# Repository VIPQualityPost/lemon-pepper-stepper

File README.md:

# Lemon Pepper Stepper Driver
Small, all in one hybrid stepper + BLDC driver, designed to mount to the back of NEMA 14/17 size stepper motors. The board supports up to 48V @ 1.5A with a choice of either step-dir, CAN bus, I2C, UART or USB input. Additionally, there are 5 GPIO broken out that can be used for a second encoder (AB hardware encoder or I2C), endstops or other general purposes. Current sensing is also included on-board.
The boards can easily be assembled by JLC and the design has been cost-optimized, coming in at about $20 per board fully assembled (minus connectors, which need to be modified to sit flat on motor back). 

Due to the high pole pair count of stepper motors, a high resolution (21 bit) magnetic encoder is used, supporting both SPI and hardware ABI position encoding. 
Despite the rather high theoretical performance of this board I think you would need some serious cooling to actually hit the potential 50-70W specs of the parts. A heatsink has been designed and produced that works well with the board, giving a uniform back profile and small fins for heat dissipation.

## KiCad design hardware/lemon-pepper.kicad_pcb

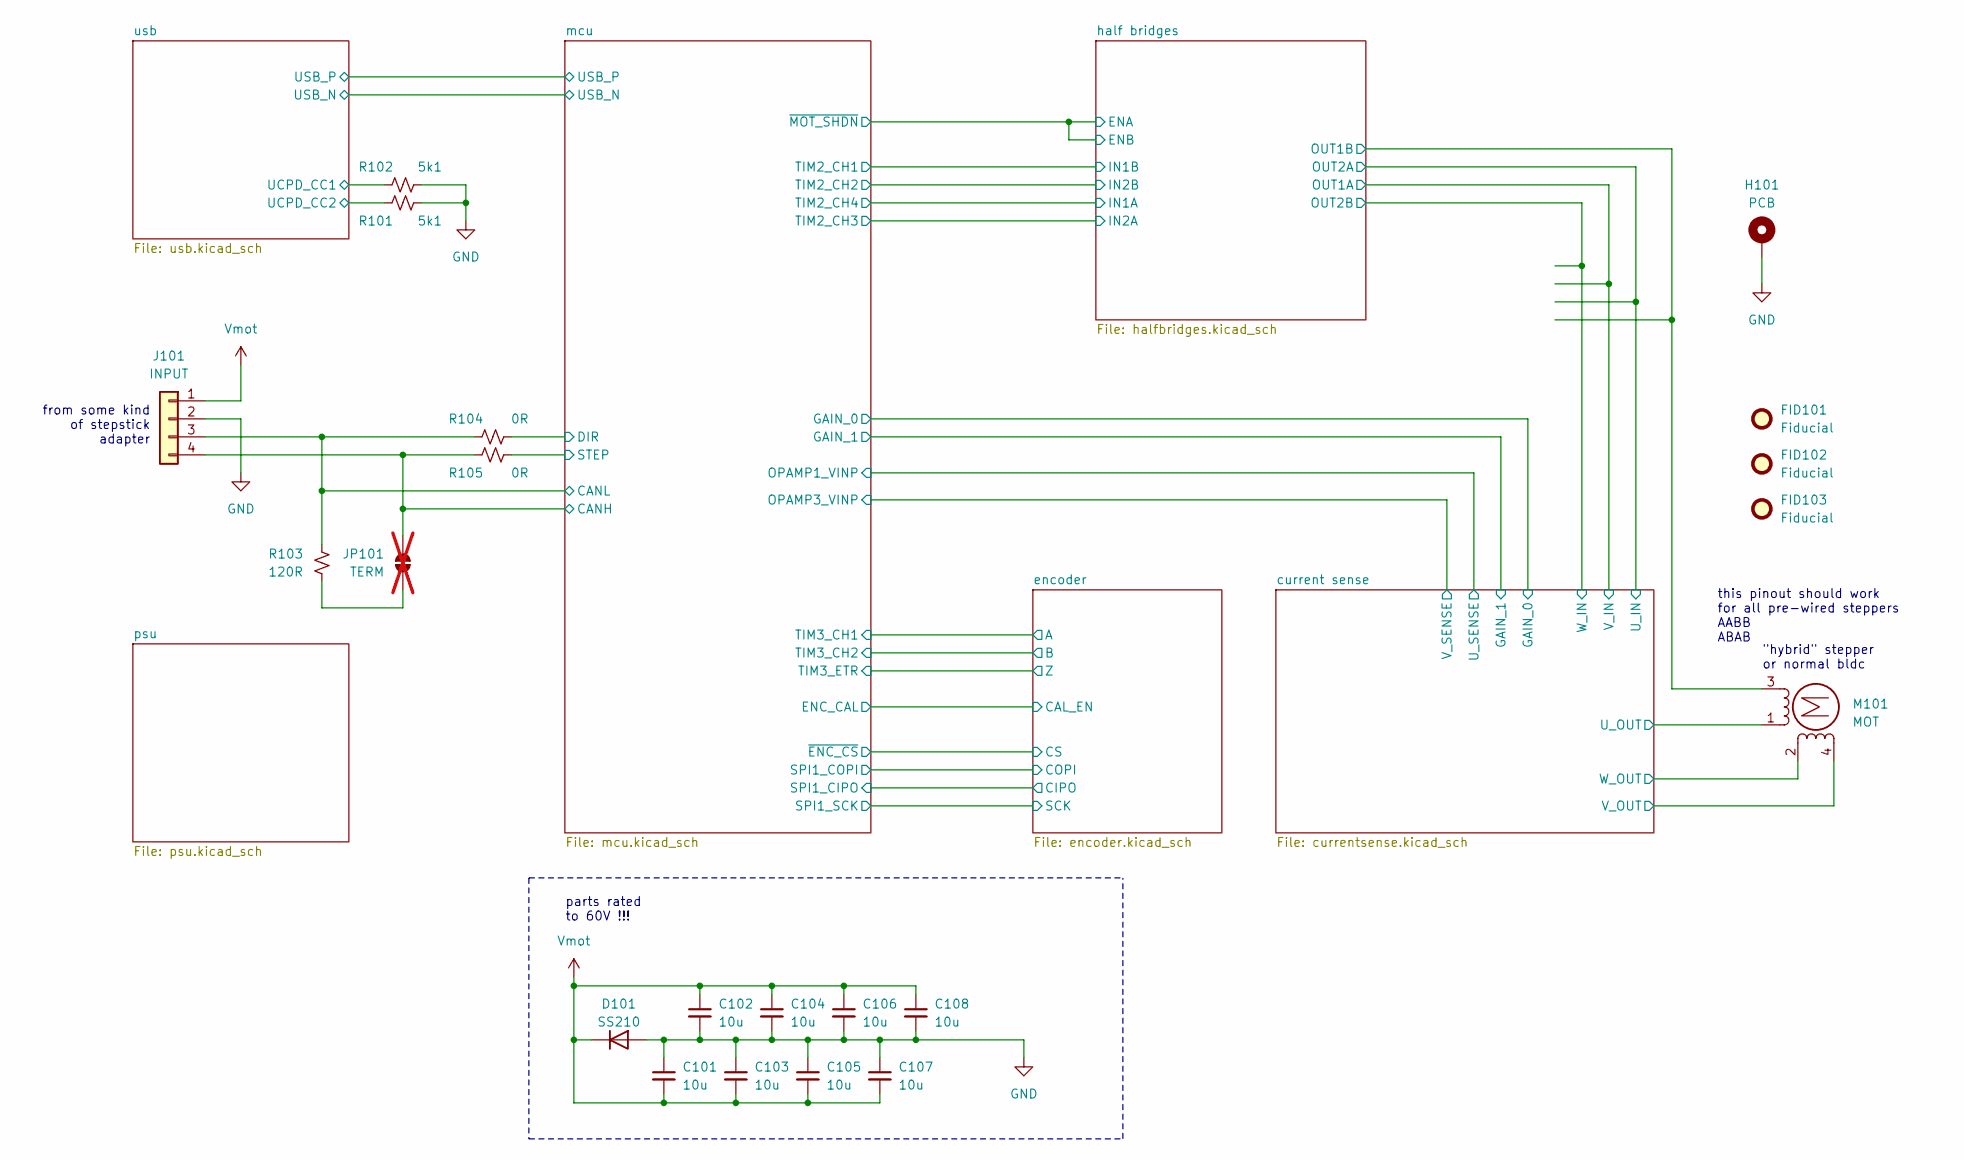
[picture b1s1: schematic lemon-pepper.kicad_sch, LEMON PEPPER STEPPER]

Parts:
C101, C102, C103, C104, C105, C106, C107, C108: 10u; C_0805_2012Metric; LCSC ID C440198
D101: SS210; D_SMA; LCSC ID C14996
FID101, FID102, FID103: Fiducial; Fiducial_0.5mm_Mask1mm
H101: PCB; nema-14-17-hybrid
J101: INPUT; JST_XH_B4B-XH-A_1x04_P2.50mm_Vertical
JP101: TERM; R_0402_1005Metric; not fitted
M101: MOT; XH2.54 4P
R101, R102: 5k1; R_0402_1005Metric; LCSC ID C25905
R103: 120R; R_0402_1005Metric; LCSC ID C25079
R104, R105: 0R; R_0402_1005Metric; LCSC ID C17168

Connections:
/current sense/U_OUT: M101.1; also elsewhere on the board
/current sense/V_OUT: M101.4; also elsewhere on the board
/current sense/W_IN: M101.2 (-); also elsewhere on the board
/half bridges/OUT1B: M101.3; also elsewhere on the board
/mcu/CANH: J101.4, JP101.1 (A), R105.2; also elsewhere on the board
/mcu/CANL: J101.3, R103.1, R104.1; also elsewhere on the board
/mcu/DIR: R104.2; also elsewhere on the board
/mcu/STEP: R105.1; also elsewhere on the board
/usb/UCPD_CC1: R102.1; also elsewhere on the board
/usb/UCPD_CC2: R101.2; also elsewhere on the board
GND: C101.1, C102.2, C103.1, C104.2, C105.1, C106.2, C107.1, C108.2, D101.2 (A), H101.1, J101.2, R101.1, R102.2; also elsewhere on the board
unnamed: JP101.2 (B), R103.2
Vmot: C101.2, C102.1, C103.2, C104.1, C105.2, C106.1, C107.2, C108.1, D101.1 (K), J101.1; also elsewhere on the board

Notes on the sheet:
this pinout should work for all pre-wired steppers AABB ABAB
parts rated to 60V !!!
from some kind of stepstick adapter
"hybrid" stepper or normal bldc

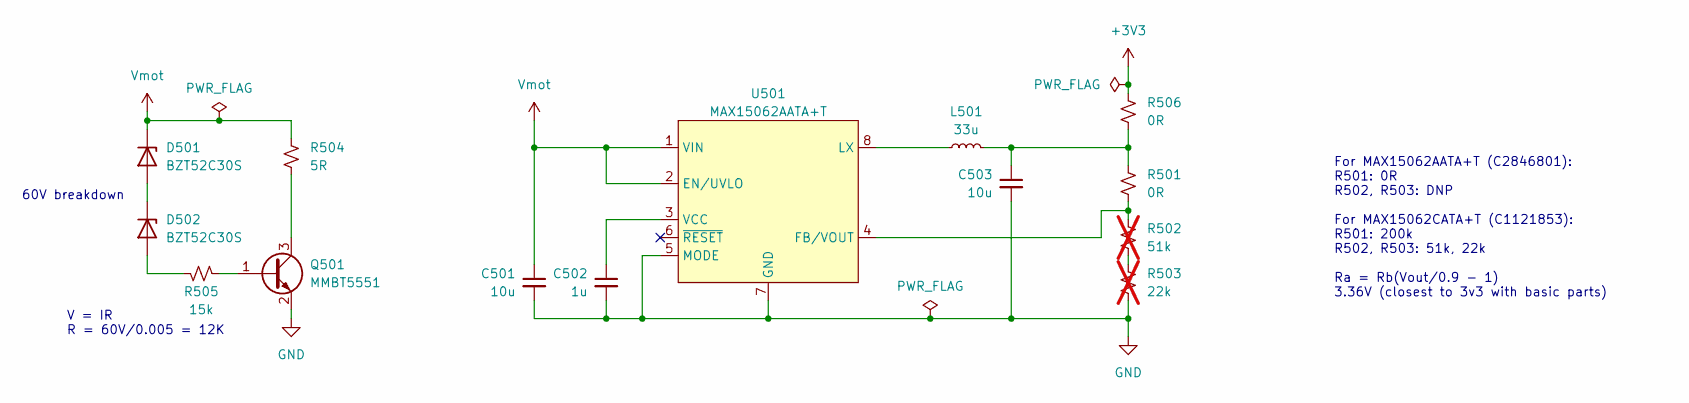
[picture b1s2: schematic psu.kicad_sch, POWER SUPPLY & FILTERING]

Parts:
C501, C503: 10u; C_0805_2012Metric; LCSC ID C440198
C502: 1u; C_0402_1005Metric; LCSC ID C52923
D501, D502: BZT52C30S; D_SOD-323; LCSC ID C19077418
L501: 33u; IND-SMD_L4.0-W4.0; LCSC ID C602034
Q501: MMBT5551; SOT-23; LCSC ID C2145
R501: 0R; R_0402_1005Metric; LCSC ID C17168
R502: 51k; R_0402_1005Metric; LCSC ID C25794; not fitted
R503: 22k; R_0402_1005Metric; LCSC ID C25768; not fitted
R504: 5R; R_0603_1608Metric; LCSC ID C22936
R505: 15k; R_0402_1005Metric; LCSC ID C25756
R506: 0R; R_0603_1608Metric; LCSC ID C21189
U501: MAX15062AATA+T; TDFN-8-1EP_2x2mm_P0.5mm_EP0.8x1.2mm; LCSC ID C2846801

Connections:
+3V3: R506.1; also elsewhere on the board
GND: C501.2, C502.2, C503.2, Q501.2 (E), R503.2, U501.5 (MODE), U501.7 (GND); also elsewhere on the board
unnamed: C503.1, L501.2, R501.1, R506.2
unnamed: D501.2 (A), D502.1 (K)
unnamed: D502.2 (A), R505.1
unnamed: Q501.1 (B), R505.2
unnamed: Q501.3 (C), R504.2
unnamed: R502.2, R503.1
unnamed: R501.2, R502.1, U501.4 (FB/VOUT)
unnamed: L501.1, U501.8 (LX)
unnamed: C502.1, U501.3 (VCC)
Vmot: C501.1, D501.1 (K), R504.1, U501.1 (VIN), U501.2 (EN/UVLO); also elsewhere on the board

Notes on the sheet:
60V breakdown
For MAX15062AATA+T (C2846801): R501: 0R R502, R503: DNP For MAX15062CATA+T (C1121853): R501: 200k R502, R503: 51k, 22k Ra = Rb(Vout/0.9 - 1) 3.36V (closest to 3v3 with basic parts)
V = IR R = 60V/0.005 = 12K

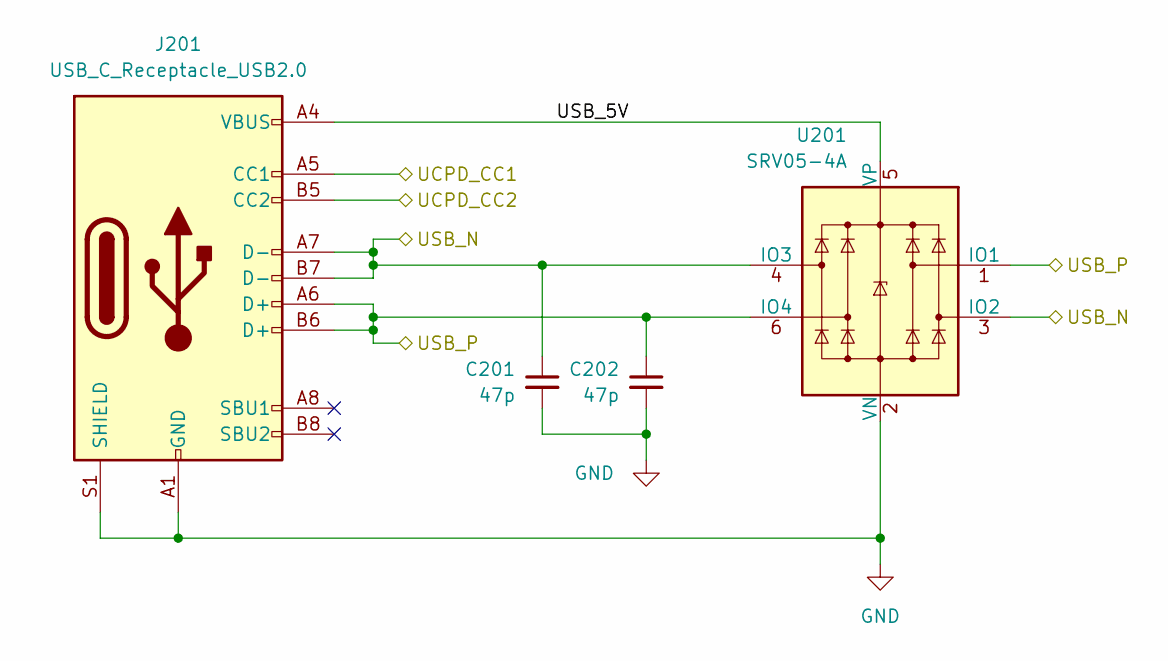
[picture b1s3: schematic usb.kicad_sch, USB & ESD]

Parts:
C201, C202: 47p; C_0402_1005Metric; LCSC ID C1567
J201: USB_C_Receptacle_USB2.0; usb_c; LCSC ID C963223
U201: SRV05-4A; SOT-23-6; LCSC ID C20615829

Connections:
/mcu/USBD_N: C201.1, J201.A7 (D-), J201.B7 (D-), U201.3 (IO2), U201.4 (IO3); also elsewhere on the board
/mcu/USBD_P: C202.1, J201.A6 (D+), J201.B6 (D+), U201.1 (IO1), U201.6 (IO4); also elsewhere on the board
/usb/UCPD_CC1: J201.A5 (CC1); also elsewhere on the board
/usb/UCPD_CC2: J201.B5 (CC2); also elsewhere on the board
/usb/USB_5V: J201.A4 (VBUS), J201.A9 (VBUS), J201.B4 (VBUS), J201.B9 (VBUS), U201.5 (VP)
GND: C201.2, C202.2, J201.A1 (GND), J201.A12 (GND), J201.B1 (GND), J201.B12 (GND), J201.S1 (SHIELD), U201.2 (VN); also elsewhere on the board

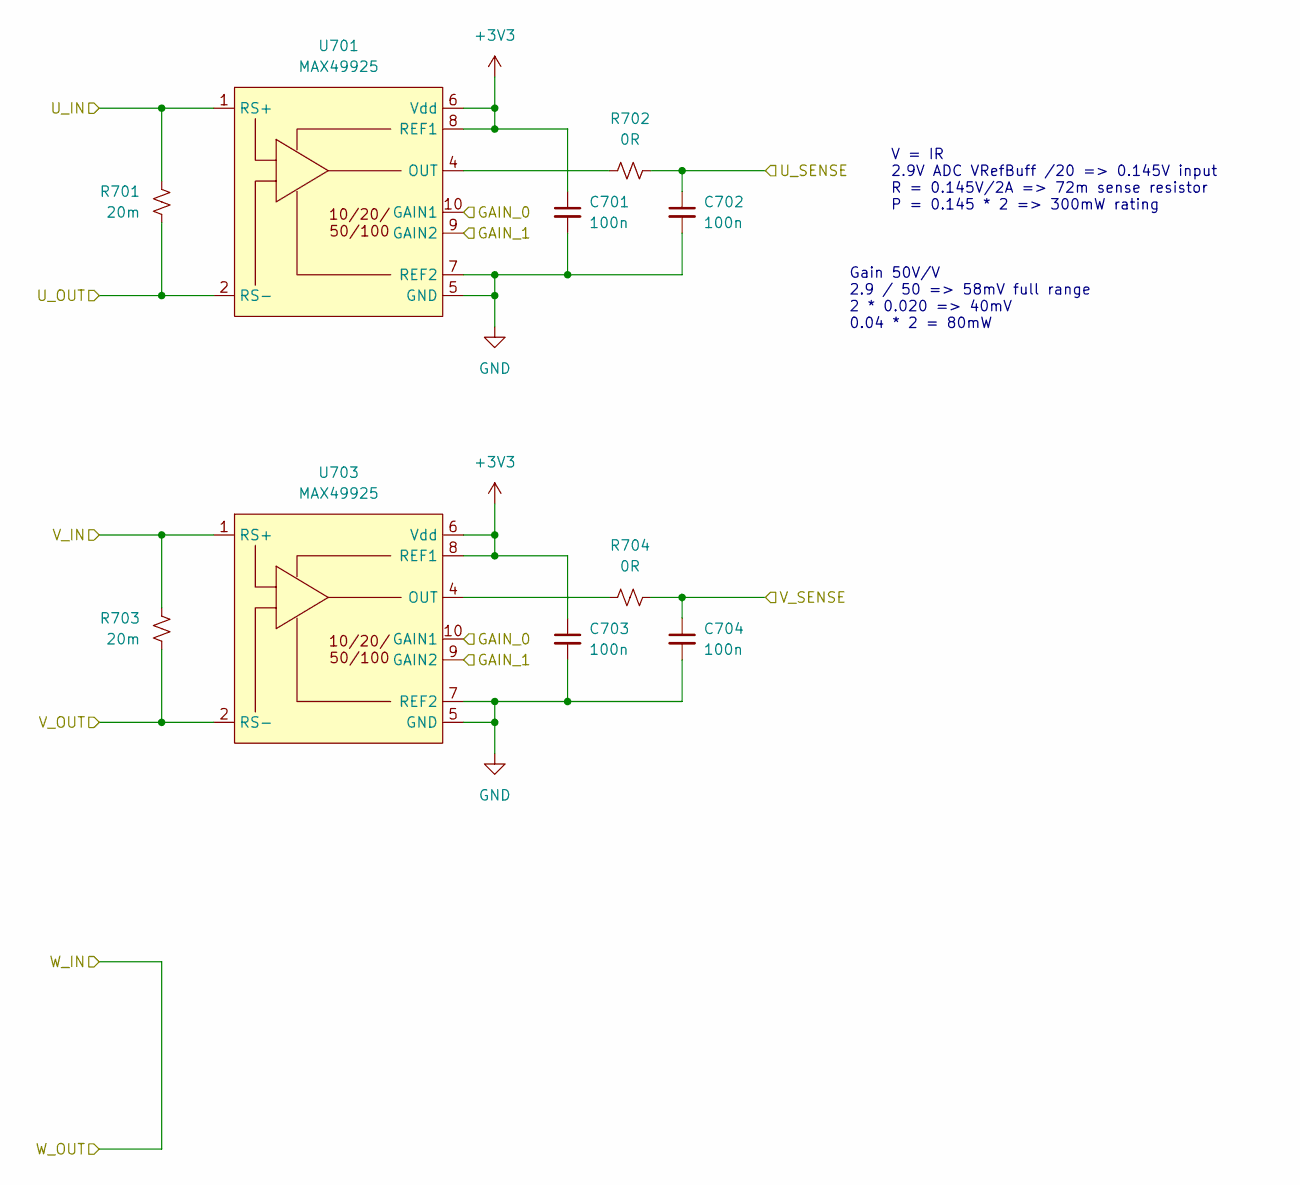
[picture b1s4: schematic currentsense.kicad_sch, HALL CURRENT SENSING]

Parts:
C701, C702, C703, C704: 100n; C_0402_1005Metric; LCSC ID C307331
R701, R703: 20m; R_1206_3216Metric; LCSC ID C393094
R702, R704: 0R; R_0402_1005Metric; LCSC ID C17168
U701, U703: MAX49925; DFN-10-1EP_3x3mm_P0.5mm_EP1.75x2.7mm; LCSC ID C19193612

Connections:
+3V3: C701.1, C703.1, U701.6 (Vdd), U701.8 (REF1), U703.6 (Vdd), U703.8 (REF1); also elsewhere on the board
/current sense/GAIN_0: U701.10 (GAIN1), U703.10 (GAIN1); also elsewhere on the board
/current sense/GAIN_1: U701.9 (GAIN2), U703.9 (GAIN2); also elsewhere on the board
/current sense/U_IN: R701.1, U701.1 (RS+); also elsewhere on the board
/current sense/U_OUT: R701.2, U701.2 (RS-); also elsewhere on the board
/current sense/U_SENSE: C702.1, R702.2; also elsewhere on the board
/current sense/V_IN: R703.1, U703.1 (RS+); also elsewhere on the board
/current sense/V_OUT: R703.2, U703.2 (RS-); also elsewhere on the board
/current sense/V_SENSE: C704.1, R704.2; also elsewhere on the board
GND: C701.2, C702.2, C703.2, C704.2, U701.5 (GND), U701.7 (REF2), U701.11 (EP), U703.5 (GND), U703.7 (REF2), U703.11 (EP); also elsewhere on the board
unnamed: R702.1, U701.4 (OUT)
unnamed: R704.1, U703.4 (OUT)

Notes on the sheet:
Gain 50V/V 2.9 / 50 => 58mV full range 2 * 0.020 => 40mV 0.04 * 2 = 80mW
V = IR 2.9V ADC VRefBuff /20 => 0.145V input R = 0.145V/2A => 72m sense resistor P = 0.145 * 2 => 300mW rating

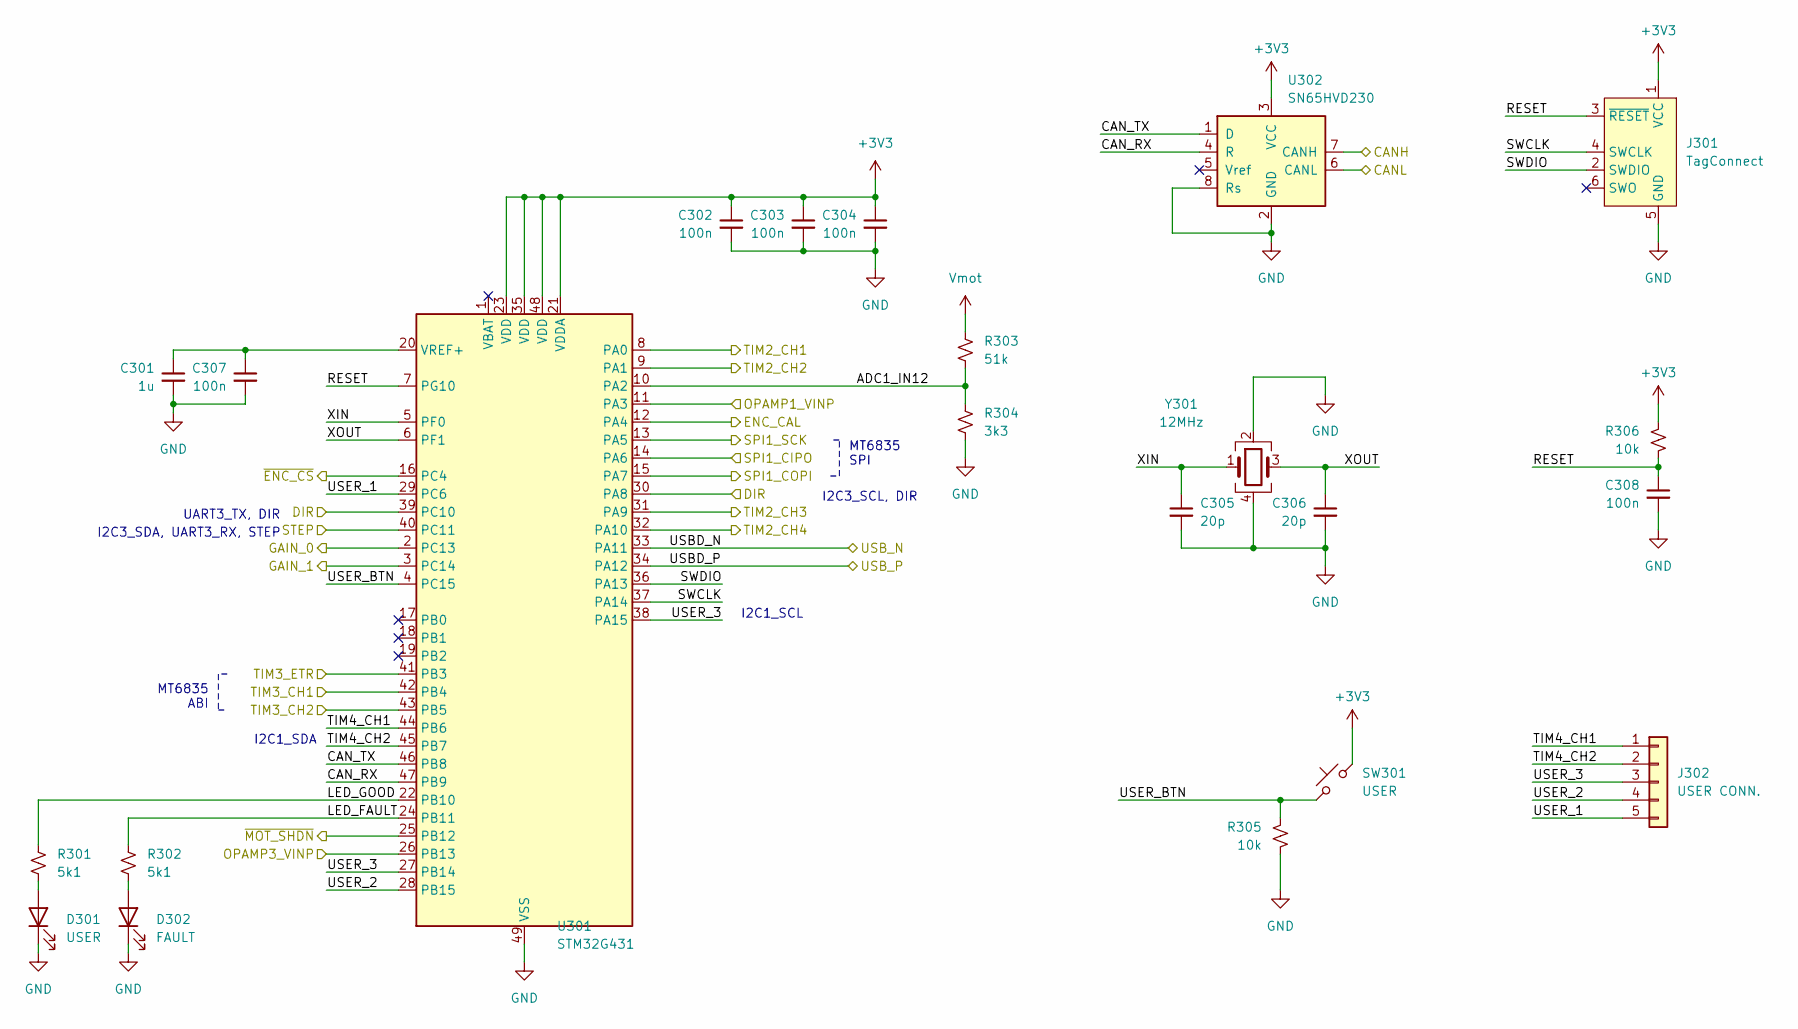
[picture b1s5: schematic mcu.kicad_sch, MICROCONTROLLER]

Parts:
C301: 1u; C_0402_1005Metric; LCSC ID C52923
C302, C303, C304, C307, C308: 100n; C_0402_1005Metric; LCSC ID C307331
C305, C306: 20p; C_0402_1005Metric; LCSC ID C1554
D301: USER; D_0603_1608Metric; LCSC ID C2290
D302: FAULT; D_0603_1608Metric; LCSC ID C2286
J301: TagConnect; Tag-Connect_TC2030-IDC-NL_2x03_P1.27mm_Vertical
J302: USER CONN.; PinHeader_1x05_P1.27mm_SMD
R301, R302: 5k1; R_0402_1005Metric; LCSC ID C25905
R303: 51k; R_0402_1005Metric; LCSC ID C25794
R304: 3k3; R_0402_1005Metric; LCSC ID C25890
R305, R306: 10k; R_0402_1005Metric; LCSC ID C25744
SW301: USER; SW_SPST_B3U-3000P; LCSC ID C963349
U301: STM32G431; QFN-48-1EP_7x7mm_P0.5mm_EP5.6x5.6mm; LCSC ID C529356
U302: SN65HVD230; SOIC-8_3.9x4.9mm_P1.27mm; LCSC ID C12084
Y301: 12MHz; Crystal_SMD_3225-4Pin_3.2x2.5mm; LCSC ID C9002

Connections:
+3V3: C302.1, C303.1, C304.1, J301.1 (VCC), R306.1, SW301.2, U301.21 (VDDA), U301.23 (VDD), U301.35 (VDD), U301.48 (VDD), U302.3 (VCC); also elsewhere on the board
/current sense/GAIN_0: U301.2 (PC13); also elsewhere on the board
/current sense/GAIN_1: U301.3 (PC14); also elsewhere on the board
/current sense/U_SENSE: U301.11 (PA3); also elsewhere on the board
/current sense/V_SENSE: U301.26 (PB13); also elsewhere on the board
/encoder/A: U301.42 (PB4); also elsewhere on the board
/encoder/B: U301.43 (PB5); also elsewhere on the board
/encoder/CAL_EN: U301.12 (PA4); also elsewhere on the board
/encoder/CIPO: U301.14 (PA6); also elsewhere on the board
/encoder/COPI: U301.15 (PA7); also elsewhere on the board
/encoder/CS: U301.16 (PC4); also elsewhere on the board
/encoder/SCK: U301.13 (PA5); also elsewhere on the board
/encoder/Z: U301.41 (PB3); also elsewhere on the board
/half bridges/ENA: U301.25 (PB12); also elsewhere on the board
/half bridges/IN1A: U301.32 (PA10); also elsewhere on the board
/half bridges/IN1B: U301.8 (PA0); also elsewhere on the board
/half bridges/IN2A: U301.31 (PA9); also elsewhere on the board
/half bridges/IN2B: U301.9 (PA1); also elsewhere on the board
/mcu/ADC1_IN12: R303.2, R304.1, U301.10 (PA2)
/mcu/CANH: U302.7 (CANH); also elsewhere on the board
/mcu/CANL: U302.6 (CANL); also elsewhere on the board
/mcu/CAN_RX: U301.47 (PB9), U302.4 (R)
/mcu/CAN_TX: U301.46 (PB8), U302.1 (D)
/mcu/DIR: U301.30 (PA8), U301.39 (PC10); also elsewhere on the board
/mcu/LED_FAULT: R302.1, U301.24 (PB11)
/mcu/LED_GOOD: R301.1, U301.22 (PB10)
/mcu/RESET: C308.1, J301.3 (~RESET), R306.2, U301.7 (PG10)
/mcu/STEP: U301.40 (PC11); also elsewhere on the board
/mcu/SWCLK: J301.4 (SWCLK), U301.37 (PA14)
/mcu/SWDIO: J301.2 (SWDIO), U301.36 (PA13)
/mcu/TIM4_CH1: J302.1, U301.44 (PB6)
/mcu/TIM4_CH2: J302.2, U301.45 (PB7)
/mcu/USBD_N: U301.33 (PA11); also elsewhere on the board
/mcu/USBD_P: U301.34 (PA12); also elsewhere on the board
/mcu/USER_1: J302.5, U301.29 (PC6)
/mcu/USER_2: J302.4, U301.28 (PB15)
/mcu/USER_3: J302.3, U301.27 (PB14), U301.38 (PA15)
/mcu/USER_BTN: R305.1, SW301.1, U301.4 (PC15)
/mcu/XIN: C305.1, U301.5 (PF0), Y301.1
/mcu/XOUT: C306.1, U301.6 (PF1), Y301.3
GND: C301.2, C302.2, C303.2, C304.2, C305.2, C306.2, C307.2, C308.2, D301.1 (K), D302.1 (K), J301.5 (GND), R304.2, R305.2, U301.49 (VSS), U302.2 (GND), U302.8 (Rs), Y301.2, Y301.4; also elsewhere on the board
unnamed: D301.2 (A), R301.2
unnamed: D302.2 (A), R302.2
unnamed: C301.1, C307.1, U301.20 (VREF+)
Vmot: R303.1; also elsewhere on the board

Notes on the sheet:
MT6835 ABI
I2C3_SDA, UART3_RX, STEP
I2C1_SDA
I2C1_SCL
MT6835 SPI
I2C3_SCL, DIR
UART3_TX, DIR

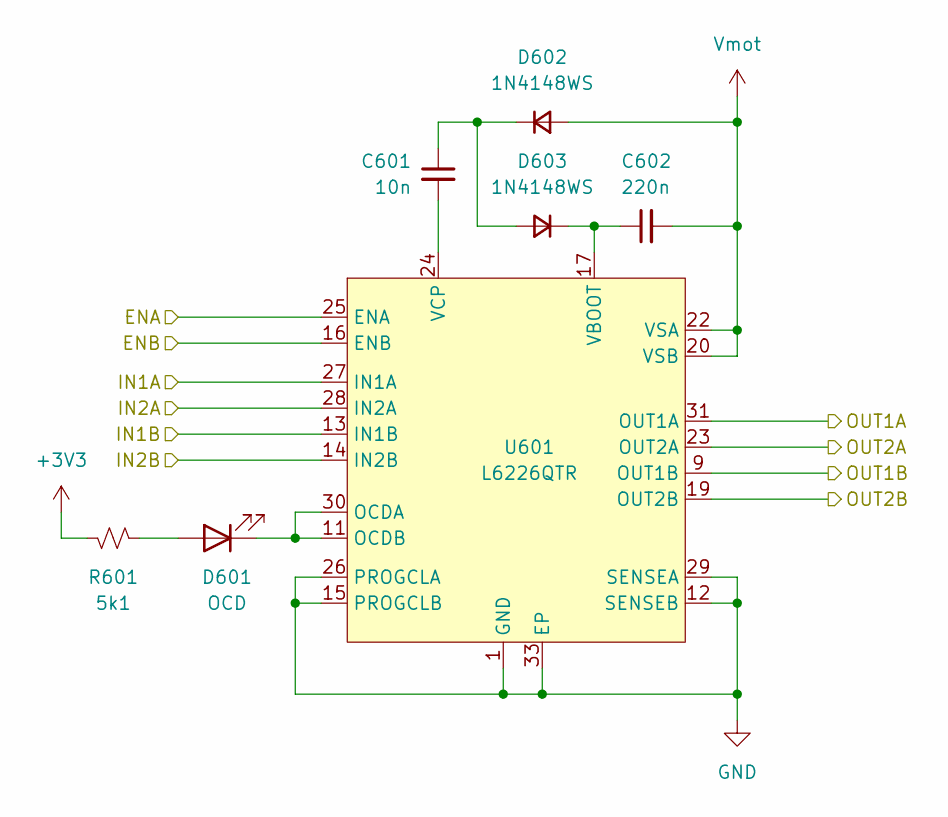
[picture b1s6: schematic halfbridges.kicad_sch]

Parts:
C601: 10n; C_0402_1005Metric; LCSC ID C15195
C602: 220n; C_0402_1005Metric; LCSC ID C16772
D601: OCD; D_0603_1608Metric; LCSC ID C2286
D602, D603: 1N4148WS; D_SOD-323; LCSC ID C2128
R601: 5k1; R_0402_1005Metric; LCSC ID C25905
U601: L6226QTR; ST-L6226Q-VQFN32; LCSC ID C95357

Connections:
+3V3: R601.2; also elsewhere on the board
/current sense/U_IN: U601.23 (OUT2A); also elsewhere on the board
/current sense/V_IN: U601.31 (OUT1A); also elsewhere on the board
/current sense/W_IN: U601.19 (OUT2B); also elsewhere on the board
/half bridges/ENA: U601.16 (ENB), U601.25 (ENA); also elsewhere on the board
/half bridges/IN1A: U601.27 (IN1A); also elsewhere on the board
/half bridges/IN1B: U601.13 (IN1B); also elsewhere on the board
/half bridges/IN2A: U601.28 (IN2A); also elsewhere on the board
/half bridges/IN2B: U601.14 (IN2B); also elsewhere on the board
/half bridges/OUT1B: U601.9 (OUT1B); also elsewhere on the board
GND: U601.1 (GND), U601.2 (NC), U601.3 (NC), U601.4 (NC), U601.5 (NC), U601.6 (NC), U601.7 (NC), U601.8 (NC), U601.12 (SENSEB), U601.15 (PROGCLB), U601.21 (GND), U601.26 (PROGCLA), U601.29 (SENSEA), U601.33 (EP); also elsewhere on the board
unnamed: D601.2 (A), R601.1
unnamed: D601.1 (K), U601.11 (OCDB), U601.30 (OCDA)
unnamed: C601.1, D602.1 (K), D603.2 (A)
unnamed: C602.1, D603.1 (K), U601.17 (VBOOT)
unnamed: C601.2, U601.24 (VCP)
Vmot: C602.2, D602.2 (A), U601.20 (VSB), U601.22 (VSA); also elsewhere on the board

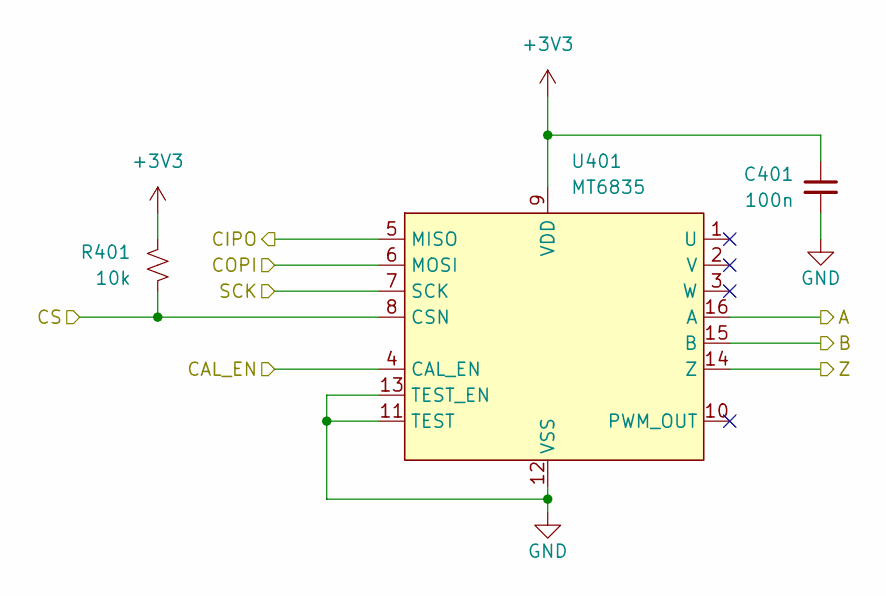
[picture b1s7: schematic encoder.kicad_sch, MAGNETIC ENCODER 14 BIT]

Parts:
C401: 100n; C_0402_1005Metric; LCSC ID C307331
R401: 10k; R_0402_1005Metric; LCSC ID C25744
U401: MT6835; TSSOP-16_4.4x5mm_P0.65mm; LCSC ID C2932578

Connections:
+3V3: C401.1, R401.1, U401.9 (VDD); also elsewhere on the board
/encoder/A: U401.16 (A); also elsewhere on the board
/encoder/B: U401.15 (B); also elsewhere on the board
/encoder/CAL_EN: U401.4 (CAL_EN); also elsewhere on the board
/encoder/CIPO: U401.5 (MISO); also elsewhere on the board
/encoder/COPI: U401.6 (MOSI); also elsewhere on the board
/encoder/CS: R401.2, U401.8 (CSN); also elsewhere on the board
/encoder/SCK: U401.7 (SCK); also elsewhere on the board
/encoder/Z: U401.14 (Z); also elsewhere on the board
GND: C401.2, U401.11 (TEST), U401.12 (VSS), U401.13 (TEST_EN); also elsewhere on the board

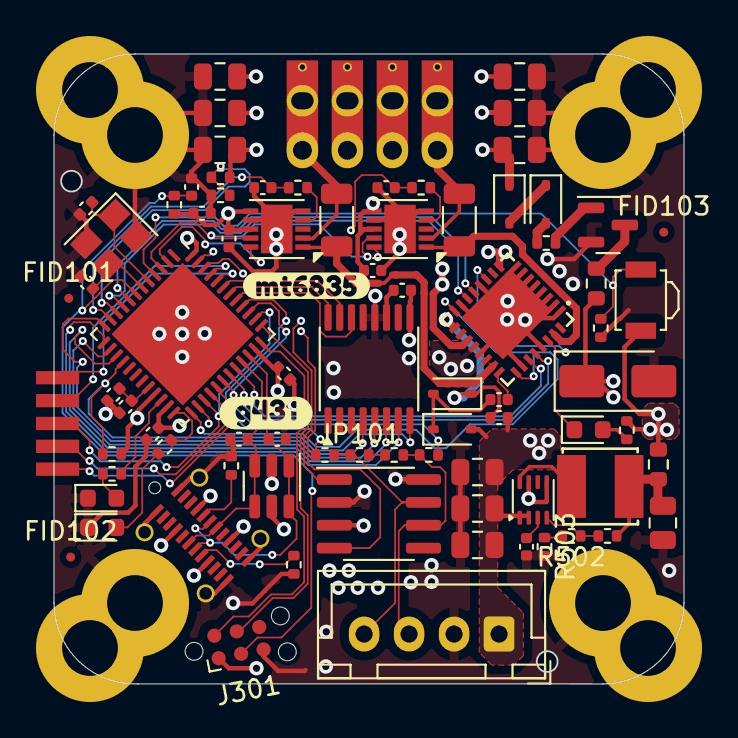
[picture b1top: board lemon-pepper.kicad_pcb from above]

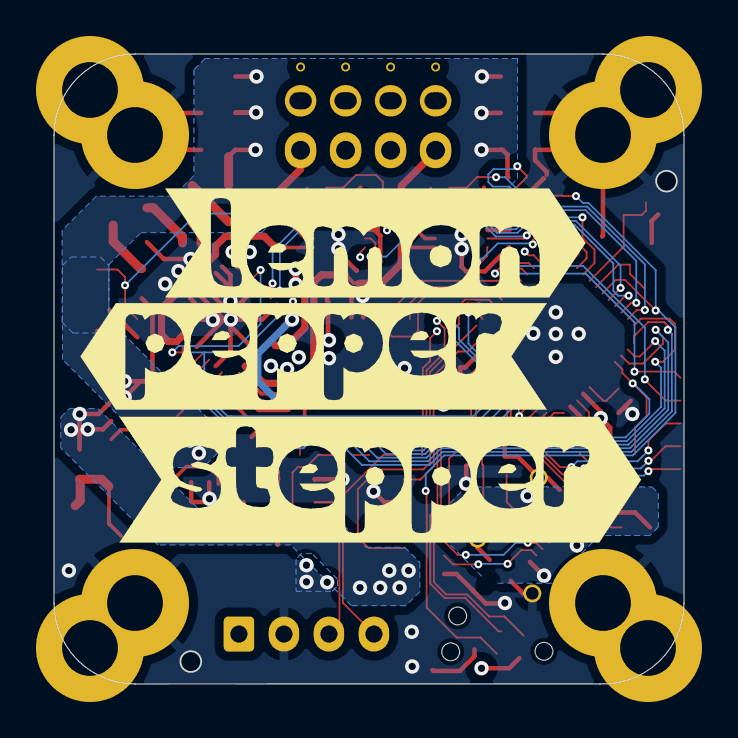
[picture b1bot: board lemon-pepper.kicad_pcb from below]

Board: 4 copper layers, 35.0 x 35.0 mm, 87 parts (3 on the bottom side), 71 nets.

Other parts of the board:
kibuzzard-652C57F7: G***; kibuzzard-652C57F7
kibuzzard-652C580D: G***; kibuzzard-652C580D
kibuzzard-694B0394: G***; kibuzzard-694B0394
kibuzzard-6557D15D: G***; kibuzzard-6557D15D
kibuzzard-6557D149: G***; kibuzzard-6557D149
kibuzzard-6557D153: G***; kibuzzard-6557D153

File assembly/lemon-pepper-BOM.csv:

Comment,Designator,Footprint,JLCPCB Part #
10u,"C101, C102, C103, C104, C105, C106, C107, C108, C501, C503",805,C440198
47p,"C201, C202",402,C1567
1u,"C301, C502",402,C52923
100n,"C302, C303, C304, C307, C308, C401, C701, C702, C703, C704",402,C307331
20p,"C305, C306",402,C1554
10n,C601,402,C15195
220n,C602,402,C16772
SS210,D101,SMA,C14996
USER,D301,603,C72041
FAULT,D302,603,C2286
BZT52C30S,"D501, D502",SOD-323,C22622
OCD,D601,603,C2286
1N4148WS,"D602, D603",SOD-323,C2128
USB_C_Receptacle_USB2.0,J201,USB C,C963223
33u,L501,IND-SMD_L4.0-W4.0,C602034
MMBT5551,Q501,SOT-23,C2145
5k1,"R101, R102, R301, R302, R601",402,C25905
120R,R103,402,C25079
0R,"R104, R105, R501, R702, R704",402,C17168
51k,R303,402,C25794
3k3,R304,402,C25890
10k,"R305, R306, R401",402,C25744
5R,R504,603,C22936
15k,R505,402,C25756
0R,R506,603,C21189
20m,"R701, R703",1206,C393094
USER,SW301,B3U-3000P,C963349
SRV05-4,U201,SOT-23-6,C7420376
STM32G431,U301,QFN48,C529356
SN65HVD230,U302,SOIC8,C12084
MT6835,U401,TSSOP-16,C2932578
MAX15062AATA+T,U501,TDFN-8,C2846801
L6226QTR,U601,VQFN-32,C95357
MAX49925,"U701, U703",DFN-10,C19193612
12MHz,Y301,3225,C9002

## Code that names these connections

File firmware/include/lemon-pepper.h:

#pragma once

#ifdef LEMONPEPPER

// MOTOR DRIVER L6226
#define U_PWM       PA10    // TIM2_CH4
#define V_PWM       PA9     // TIM2_CH3
#define W_PWM       PA1     // TIM2_CH2

#define MOT_A1      PA0     // TIM2_CH1
#define MOT_A2      PA10    // TIM2_CH4
#define MOT_B1      PA9     // TIM2_CH3
#define MOT_B2      PA1     // TIM2_CH2

#define MOT_EN      PB12

// ENCODER MT6835
#define ENC_A       PB4     // TIM3_CH1
#define ENC_B       PB5     // TIM3_CH2
#define ENC_Z       PB3     // TIM3_ETR

#define ENC_COPI    PA7     // SPI1_MOSI
#define ENC_CIPO    PA6     // SPI1_MISO
#define ENC_SCK     PA5     // SPI1_SCK
#define ENC_CS      PC4     

#define CAL_EN      PA4

// CURRENT SENSE
#define ISENSE_U    PA3     // VOPAMP1_P, ADC1_IN4
#define ISENSE_V    PB13    // VOPAMP3_P

/**
 * 0b00 10V/V
 * 0b01 20V/V
 * 0b10 50V/V
 * 0b11 100V/V
*/
#define ISENSEGAIN_0 PC13   // GAIN0 
#define ISENSEGAIN_1 PC14   // GAIN1

// COMMUNICATION
/** 
 * Note that you can only use one input peripheral 
 * at a time. If  you want to use CANbus you also have 
 * to remove the resistors that join step-dir to CAN H/L
 * R104 R105 to protect MCU from high common mode voltages.
*/
#define CAN_TX      PB8
#define CAN_RX      PB9

#define UART3_TX    PC10
#define UART3_RX    PC11

#define I2C3_SDA    PC11
#define I2C3_SCL    PA8

#define STEP_PIN    PC10
#define DIR_PIN     PC11

// USER CONNECTOR
/**
 * Additional timer available for encoder interface. 
 * If not using, there are 5 GPIO available.
*/
#define USER_ENCA   PB6     // TIM4_CH1
#define USER_ENCB   PB7     // TIM4_CH2

#define USER1       PC6
#define USER2       PB15
#define USER3       PB14
#define USER4       PB7
#define USER5       PB6

// MISC
#define USER_BUTTON PC15
#define LED_GOOD    PB10
#define LED_FAULT   PB11
#define MOT_VOLTAGE PA2     //ADC1_IN3

#endif

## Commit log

2023-10-07 add cubemx pinout
2023-10-07 restructure
2023-10-12 finish component selection
2023-10-12 reverse polarity diode
2023-10-12 update pdf
2023-10-17 try new driver
2023-10-18 change driver configuration
2023-10-18 finish layout and prod files
2023-10-18 board logo
2023-10-19 update fab files
2023-10-19 fix fab files (again)
2023-10-20 rework power plane
2023-10-20 add readme and update fab files
2023-10-20 readme typo
2023-10-20 oh my god fix the readme
2023-10-20 tweak pours
2023-10-22 work on analog layout
2023-10-22 finallize rev 1 layout
2023-10-22 firmware defines
2023-10-22 add firmware defines
2023-10-22 fix current sense pn
2023-10-22 shift B1 trace slightly
2023-10-23 clean up ERC in schematic
2023-10-23 change vias to 0.2/0.45mm for cheaper production
2023-10-23 roll nema14 and nema17 into same branch
2023-10-24 change pins to support I2C input
2023-10-26 fix via sizing
2023-10-28 update firmware defines to support pcb rev 2
2023-11-02 fix bringup issues
2023-11-02 start on firmware
2023-11-02 remove stray files/folders
2023-11-06 start working on current sense
2023-11-08 bringup changes
2023-11-09 redraw USB C connector with proper mounting holes
2023-11-09 work on current sense
2023-11-10 try to fix submodule
2023-11-11 Change references to BLDCDriver to FOCDriver in current sense base class
    change setPwm function in FOCDriver to accept 3 args, with a default value for the 3rd
    Change stepper driver classes to use 3 arg setPwm, ignoring 3rd arg.
    created InlineCurrentSenseSync class in lib/currentsense.
    fixed timer bug in calibrate encoder, in main
    defined a label for serialusb, to make it easier to swap out.
2023-11-11 Add some debug prints
    fix function def for init ADC, so it overrides the weak generic version
    fix caps in mt6835 include so gcc is happy
2023-11-11 add idea for heatsink NEMA14
2023-11-11 update pcb layout
2023-11-12 fix clock tree
2023-11-12 current sense LPF prototype
2023-11-12 heatink prototype
2023-11-12 get ADC trigger working
2023-11-12 try unity gain
2023-11-13 Fix calls to init opamp3 based on cubeMX.
2023-11-13 improve DFM
2023-11-14 add user button
2023-11-14 tinker with dma
2023-11-14 fix thermal contact placement
2023-11-15 got current sense readings!
2023-11-15 add vmotor pin in gpio init
2023-11-15 oops msp deinit
2023-11-15 fix opamp instance fix voltage scale in utils.cpp fix switch case for pins in _readADCVoltageInline
    added commented out lines for my motor config, changed PID values, added global monitor variables near loop
2023-11-17 finalize v3 files
2023-11-17 update step file
2023-11-18 rev3 documentation
2023-11-18 add DFU button. update defines for v3
2023-11-19 Add torque controller options into loopFOC
    add current feed forward to loopFOC
    add ABCurrent_s def to foc_utils for current sense.
    add virtual function defs to base current sense class
    add functions to InlineCurrentSenseSync to get AB and DQ currents, along with their declarations
2023-12-05 remove OPA2 for rev 3
2023-12-10 change inductor footprint, add I2C1 SCL on user 3
2023-12-10 update documentation
2023-12-18 update L6226Q footprint and symbol
2024-01-13 v3 fixes, appropriate inductor
2024-01-13 Changed initial motor setpoint to the current angle, so that motor doesn't make a violent move on startup
2024-01-23 Made analog gain of current sense amps selectable by mcu. Removed analog ground plane and tied all grounds together
2024-01-30 get DRC clean
2024-01-30 add tooling holes, update CPL
2024-02-06 Update firmware defines to match hardware
2024-02-28 add scripts
2024-02-28 fix erc failures
2024-03-01 Push schematics to repo via gha
2024-03-01 head flag
2024-03-01 token
2024-03-01 change head branch of pr
2024-03-01 commit to main
2024-03-01 commit to HEAD
2024-03-01 Add design file PDFs to repo [skip ci]
2024-03-01 try gha pr again
2024-03-01 pull before push
2024-03-01 add fetch
2024-03-01 remove pull as fetch should fix
2024-03-01 Move PR from design review to documentation generation
2024-03-01 forgot to add design.yml
2024-03-05 fix current sense pinout
2024-03-05 Try to get documentation flow working
2024-03-05 Remove assembly folder as now documentation comes from artifact
2024-03-05 Remove vesitgal files
2024-03-05 Update BOM field LCSC ID
2024-03-06 add firmware control of current sense gain pins add commented call to initialize current sense object
2024-05-05 Fix github action
2024-05-05 Fix zip paths
2024-05-05 Fix zip file
2024-05-05 Remove nested folder
2024-05-05 Move gerber outputs up a directory
2024-05-05 Remove unused gerberjob file
2024-06-13 Fix missing edge cuts in workflow
2024-06-24 add mechanical models
2025-11-10 update to kicad 9
2025-11-10 patch up CI
2025-11-10 Fix CPL formatter
2025-11-10 fix BOM to use basic parts again
2025-11-10 Add MIT License to the project
2025-11-18 bump trace width in key areas
2025-11-18 fix inductor input trace
2025-12-23 add hybrid board outline
2025-12-23 clean erc drc, pack sym, footprints into standalone lib
2025-12-24 add step model for new heatsink
